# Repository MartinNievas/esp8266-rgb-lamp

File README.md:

# ESP8266 RGB LAMP
WiFi ESP8266 rgb-lamp color picker

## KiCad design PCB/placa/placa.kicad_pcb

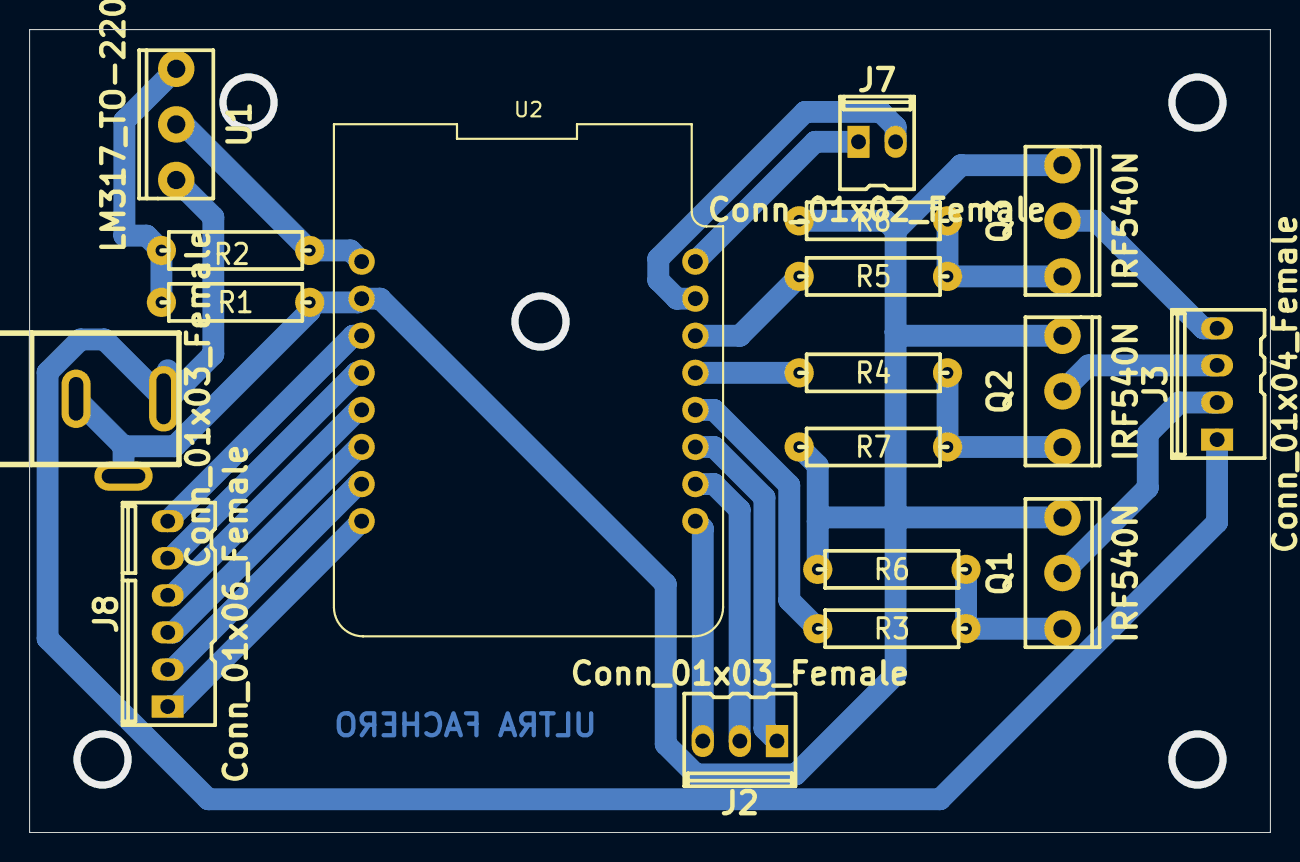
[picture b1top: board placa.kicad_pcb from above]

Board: 2 copper layers, 85.0 x 55.0 mm, 18 parts (0 on the bottom side), 24 nets.

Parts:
J1: Conn_01x03_Female; dc_socket
J2: Conn_01x03_Female; kk100_22-23-2031
J3: Conn_01x04_Female; kk100_22-23-2041
J7: Conn_01x02_Female; kk100_22-23-2021
J8: Conn_01x06_Female; kk100_22-23-2061
Q1, Q2, Q3: IRF540N; to220
R1: 3K; RC05
R2, R3, R4, R5: 1K; RC05
R6, R7, R8: 10K; RC05
U1: LM317_TO-220; to220
U2: WeMos_D1_mini; wemos-d1-mini-with-pin-header

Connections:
+5V: R2.1, U1.2, U2.9
/BLUE_LED: R5.2, U2.6
/GREEN_LED: R4.2, U2.5
/POWER: J1.3, J3.1, U1.3
/RED_LED: R3.2, U2.4
GND: J1.1, J1.2, Q1.3, Q2.3, Q3.3, R1.2, R6.2, R7.2, R8.2, U2.10
unnamed: J2.1, U2.3
unnamed: J2.2, U2.2
unnamed: J2.3, U2.1
unnamed: J3.2, Q1.2
unnamed: J3.3, Q2.2
unnamed: J3.4, Q3.2
unnamed: J7.1, U2.8
unnamed: J7.2, U2.7
unnamed: J8.1, U2.16
unnamed: J8.2, U2.15
unnamed: J8.3, U2.14
unnamed: J8.4, U2.13
unnamed: J8.5, U2.12
unnamed: J8.6, U2.11
unnamed: Q1.1, R3.1, R6.1
unnamed: Q2.1, R4.1, R7.1
unnamed: Q3.1, R5.1, R8.1
unnamed: R1.1, R2.2, U1.1
